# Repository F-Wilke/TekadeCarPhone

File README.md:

# TekadeCarPhone Hardware Design

This repository contains the KiCad source files for the **Tekade Car Phone** electronics, including the main baseboard, standalone UI board, libraries, production outputs, and reference documentation.

## Project Contents

- **Main design (CM4-based baseboard)**
  - Project: `ReleaseDeviceDigitalAudio.pro`
  - Top schematic: `ReleaseDeviceDigitalAudio.sch`
  - PCB: `ReleaseDeviceDigitalAudio.kicad_pcb`
  - Hierarchical sheets include:
    - `RaspberryPiCM4.sch`
    - `PowerSupplyCM4.sch`
    - `AudioMixing.sch`
    - `BluetoothModule.sch`
    - `ControllerUIBoard.sch`
    - `7SegmentDriver.sch`
    - `LevelShift.sch`
    - `RTC.sch`

- **Standalone UI board**
  - Project: `UIBoardStandalone.pro`
  - Schematic: `UIBoardStandalone.sch`
  - PCB: `UIBoardStandalone.kicad_pcb`

- **Alternative/legacy CM3 files**
  - `RaspberryPiCM3.sch`
  - `PowerSupplyCM3.sch`

- **Production and supporting assets**
  - Gerbers: `Gerber/`
  - BOM history: `BOM/`
  - Component datasheets/reference designs: `Datasheets/`
  - Custom symbols/footprints/libs: `libs/`

## Main Components and Their Roles

The CM4 baseboard design is split into functional blocks. The key components used in each block are:

- **Host compute module (`RaspberryPiCM4.sch`)**
  - Raspberry Pi Compute Module 4 is the main processing unit and system controller.

- **User/control interface (`ControllerUIBoard.sch`)**
  - **ATmega4809-A** handles local UI/control tasks and bridges signals between peripherals and the CM4.
  - External connectors and protection/passive networks support buttons, status signals, and board-to-board interfaces.

- **Audio codec and analog audio path (`AudioMixing.sch`)**
  - **MAX98089ETN+** provides the main audio codec/mixing interface (digital audio to analog paths and vice versa).
  - Supporting passives, filtering, and clocking components condition and stabilize audio signals.

- **Bluetooth audio module (`BluetoothModule.sch`)**
  - **BM64/BM83 family module** provides Bluetooth audio connectivity and related control/status interfaces.
  - **APX803L** supervisor supports reset/monitoring behavior for reliable module startup.

- **Display driving (`7SegmentDriver.sch`)**
  - **CD4514BM** and **CD4511BPWR** perform decoding/drive logic for 7-segment display control.
  - **ULN2003F12FN-7** transistor arrays provide higher-current sink drive for display segments/digits.

- **Real-time clock (`RTC.sch`)**
  - **PCF85063A** keeps time while system power is cycled.
  - Battery backup and crystal network maintain RTC operation.

- **Power entry and regulation (`PowerSupplyCM4.sch`)**
  - Automotive supply protection is implemented with TVS/clamp and filtering stages.
  - Switching/regulation and control circuitry generate stable board rails (for example +5V and +3.3V domains used by subsystems).

## Tooling

- Project files are in a legacy KiCad format (`.pro` and `EESchema Schematic File Version 4`).
- Open `.pro` projects in KiCad to browse schematics, PCB layout, and regenerate outputs.
- If using newer KiCad versions, open files carefully to avoid unintentionally migrating legacy project formats.

## Typical Workflow

1. Open `ReleaseDeviceDigitalAudio.pro` (or `UIBoardStandalone.pro`) in KiCad.
2. Review/update schematic sheets.
3. Update PCB from schematic and run DRC/ERC.
4. Regenerate fabrication outputs (Gerber + drill) and update BOM as needed.

## Notes

- This repository is focused on **hardware design artifacts**; firmware/software sources are not included.
- Some files with `-bak` suffix are backup snapshots.

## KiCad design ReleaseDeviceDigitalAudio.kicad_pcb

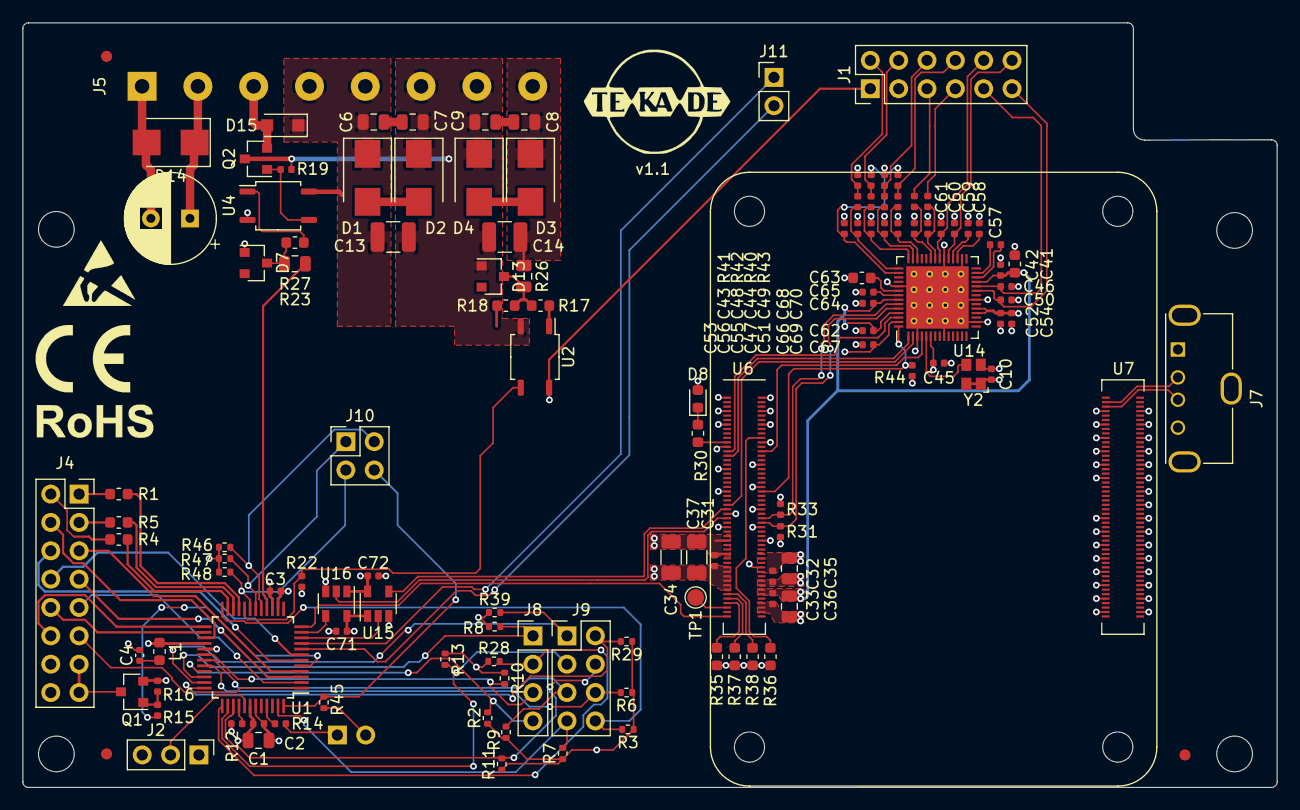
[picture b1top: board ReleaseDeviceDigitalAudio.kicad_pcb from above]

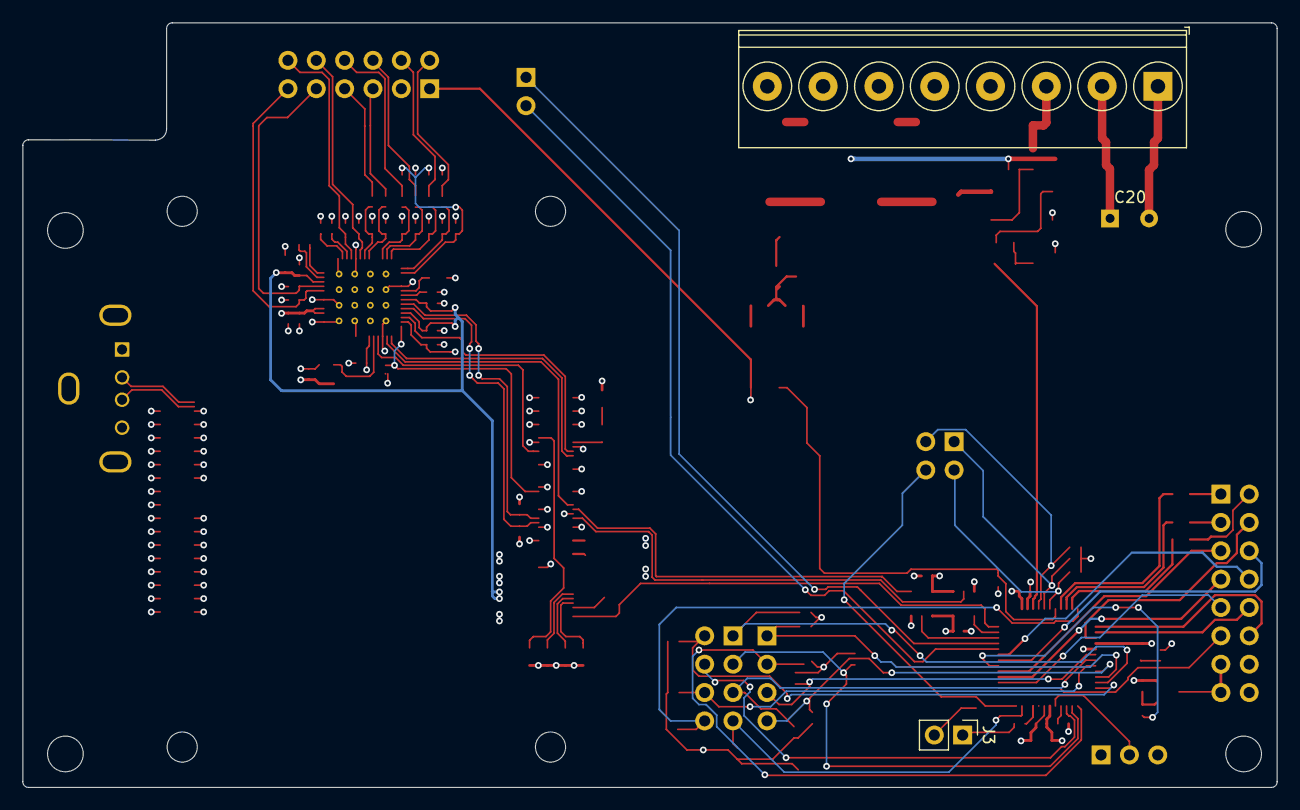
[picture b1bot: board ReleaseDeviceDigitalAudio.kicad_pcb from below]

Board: 4 copper layers, 112.4 x 68.5 mm, 129 parts (2 on the bottom side), 105 nets.

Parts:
C1: 4u7/16V/X7R; C_0805_2012Metric
C2, C3, C4, C10, C31, C32, C33, C42, C71, C72: 100n/16V/X7R; C_0402_1005Metric
C6, C7, C8, C9: 4n7/100V/X7R; C_0805_2012Metric
C13, C14: 10u/50V/X7R; C_1210_3225Metric
C20: 220u/25V; CP_Radial_D8.0mm_P3.50mm
C34, C37: 47u/10V/X5R; C_1206_3216Metric
C35, C36: 22u/10V/X5R; C_0805_2012Metric
C41: 10u/6V3/X5R; C_0603_1608Metric
C43, C44, C45, C48, C49, C52, C53, C54, C57, C58, C59, C62, C64, C65, C67, C68, C70: 1u/6V3/X5R; C_0402_1005Metric
C46, C47, C50, C51, C55, C56, C60, C61, C66, C69: 10p/50V/C0G; C_0402_1005Metric
C63: 2u2/6V3/X5R; C_0603_1608Metric
D1, D3: SMBJ28A-13-F; D_SMB
D2, D4, D14: SMBJ14A-13-F; D_SMB
D7: BZX84B5V1-7-F; SOT-23-2-DiodesInc
D8: LED_GRN; LED_0603_1608Metric
D13: BZX84B12-7-F; SOT-23-2-DiodesInc
D15: 1N4148WQ-7-F; D_SOD-123F
H1, H2, H3, H4: MountingHole; MountingHole_3.2mm_M3_DIN965
J1: Conn_02x06_Odd_Even; PinHeader_2x06_P2.54mm_Vertical
J2: ATMEGA_PROG; PinHeader_1x03_P2.54mm_Vertical
J3: SignalStrength; PinHeader_1x02_P2.54mm_Vertical
J4: UIBoardCON1; PinSocket_2x08_P2.54mm_Vertical
J5: Phoenix_PTS-1,5-8-5.0-H; TerminalBlock_Phoenix_PTS-1,5-8-5.0-H_1x08_P5.00mm_Horizont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
J7: USB_A; USB_A_Molex_105057_Vertical
J8: Conn_01x04; PinHeader_1x04_P2.54mm_Vertical
J9: Conn_02x04_Odd_Even; PinHeader_2x04_P2.54mm_Vertical
J10: Conn_02x02_Odd_Even; PinHeader_2x02_P2.54mm_Vertical
J11: Conn_01x02; PinHeader_1x02_P2.54mm_Vertical
L1: Ferrit/470R/1A/0,2R; L_0603_1608Metric
Q1: BSS314PEH6327XTSA1; SOT-23
Q2: SI2316BDS-T1-GE3; SOT-23
R1, R4, R5: 150R/1%; R_0603_1608Metric
R2, R3, R6, R7, R8, R9, R10, R11, R13, R28, R29, R39, R45, R46, R47, R48: 22k/1%; R_0402_1005Metric
R12: 100k/1%; R_0402_1005Metric
R14: 15k; R_0402_1005Metric
R15: 100R/1%; R_0402_1005Metric
R16, R19: 47k/1%; R_0402_1005Metric
R17, R18, R30: 1k/1%; R_0603_1608Metric
R22, R44: 10k/1%; R_0402_1005Metric
R23: 68R/1%; R_0805_2012Metric
R26: 150R/1%; R_0805_2012Metric
R27: 360R/1%; R_0603_1608Metric
R31, R33: NA; R_0402_1005Metric
R35, R36, R38: NA; R_0603_1608Metric
R37: 0R; R_0603_1608Metric
R40, R41, R42, R43: 2k2/1%; R_0402_1005Metric
TP1: CM4PWR; TestPoint_Pad_D1.5mm
U1: ATmega4809-A; TQFP-48_7x7mm_P0.5mm
U2, U4: VOMA617A; SOP-4_3.8x4.1mm_P2.54mm
U6: CM4_Connectors_Part1; CM4-Part1
U7: CM4_Connectors_Part2; CM4-Part2
U14: MAX98089ETN+; QFN-56_EP_7x7_Pitch0.4mm
U15, U16: SN74LV1T126; SOT-23-5
Y2: WE_830208220101; WE_IQXO-791

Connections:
+1V8: C33.1, C36.1, C41.1, C42.1, C62.1, C64.1, U6.88, U6.90, U14.25, U14.50, U14.53
+3V3: C10.1, C32.1, C35.1, C45.1, C52.1, C54.1, C67.1, C72.1, D8.2, R31.1, R33.1, R44.1, U6.78, U6.84, U6.86, U14.6, U14.18, U14.19, U14.55, U15.1, U16.5, Y2.1, Y2.4
+5V: C1.2, C2.1, C3.1, C20.1, C31.1, C34.1, C37.1, C71.1, D14.1, J1.1, J2.1, J4.14, J4.16, J5.2, J7.1, L1.1, Q1.2, R2.1, R3.1, R6.1, R7.1, R8.1, R9.1, R10.1, R11.1, R12.1, R13.1, R16.1, R28.1, R29.1, R39.1, U1.14, U1.28, U1.42, U2.4, U6.77, U6.79, U6.81, U6.83, U6.85, U6.87, U15.5, U16.1
+BATT: C6.1, C13.1, D1.1, D15.1, J5.4, J5.5, U4.4
-BATT: C7.2, C9.2, C13.2, C14.2, D2.1, D4.1, D13.2, J5.6, J5.7, Q2.3, R19.1, U2.2
/AudioMAX98089/I2S2_SD_CLK: U6.49, U14.2
/AudioMAX98089/I2S2_SD_IN: U6.25, U14.54
/AudioMAX98089/I2S2_SD_OUT: U6.27, U14.1
/AudioMAX98089/I2S2_SD_WS: U6.26, U14.4
/AudioMAX98089/MAX_MIC1N: C44.1, C47.1, U14.41
/AudioMAX98089/MAX_MIC1P: C49.1, C51.1, U14.40
/AudioMAX98089/MAX_MIC2N: C43.1, C56.1, U14.43
/AudioMAX98089/MAX_MIC2P: C48.1, C55.1, U14.42
/AudioMAX98089/MAX_MICBIAS: C53.1, R42.2, R43.1, U14.44
/AudioMAX98089/MCLK: U14.5, Y2.3
/Audio_Handset_Out_L: C60.1, J1.12, U14.33
/Audio_Handset_Out_R: C61.1, J1.10, U14.35
/Audio_Master_Out_L: C46.1, J1.9, U14.24
/Audio_Master_Out_R: C50.1, J1.11, U14.23
/ControllerUIBoard/5V_BL: J4.13, J4.15, Q1.3
/ControllerUIBoard/7Seg_Driver_BI: J4.4, U1.27
/ControllerUIBoard/7seg_dec_D1: J4.11, U1.1
/ControllerUIBoard/7seg_dec_D2: J4.7, U1.3
/ControllerUIBoard/7seg_dec_D3: J4.5, U1.4
/ControllerUIBoard/7seg_dec_D4: J4.9, U1.2
/ControllerUIBoard/7seg_dr_A: J4.6, U1.6
/ControllerUIBoard/7seg_dr_B: J4.12, U1.25
/ControllerUIBoard/7seg_dr_C: J4.10, U1.26
/ControllerUIBoard/7seg_dr_D: J4.8, U1.7
/ControllerUIBoard/AVRRESET: R12.2, U1.40
/ControllerUIBoard/Button_0: J9.7, R7.2, U1.47
/ControllerUIBoard/Button_1: J8.1, R8.2, U1.34
/ControllerUIBoard/Button_2: J9.1, R39.2, U1.35
/ControllerUIBoard/Button_3: J9.2, R29.2, U1.36
/ControllerUIBoard/Button_4: J8.2, R28.2, U1.37
/ControllerUIBoard/Button_5: J9.3, R13.2, U1.38
/ControllerUIBoard/Button_6: J9.4, R11.2, U1.39
/ControllerUIBoard/Button_7: J8.3, R10.2, U1.30
/ControllerUIBoard/Button_8: J9.5, R9.2, U1.31
/ControllerUIBoard/Button_9: J9.6, R6.2, U1.32
/ControllerUIBoard/Button_G: J10.1, R47.1, U1.18
/ControllerUIBoard/Button_M: J9.8, R3.2, U1.24
/ControllerUIBoard/Button_P: J10.3, R48.1, U1.19
/ControllerUIBoard/Button_R: J8.4, R2.2, U1.33
/ControllerUIBoard/Button_S: J10.2, R46.1, U1.17
/ControllerUIBoard/Button_X: J10.4, R45.1, U1.48
/ControllerUIBoard/Hoerer_1: J11.2, U1.8
/ControllerUIBoard/Hoerer_2: J11.1, U1.9
/ControllerUIBoard/IGNITION_SENSE: R22.2, U1.20, U2.3
/ControllerUIBoard/LED_GN: J4.2, R4.2
/ControllerUIBoard/LED_RD: J4.3, R5.2
/ControllerUIBoard/LED_YL: J4.1, R1.2
/ControllerUIBoard/RPI_RUN: U1.12, U6.99
/ControllerUIBoard/Signal_Strength_Dial_+: J3.1, R14.1
/ControllerUIBoard/UART1_RX: U1.11, U15.4
/ControllerUIBoard/UART1_TX: U1.10, U16.2
/ControllerUIBoard/UPDI_DATA: J2.2, U1.41
/HeadsetMicInN: C44.2, J1.6, R40.1
/HeadsetMicInP: C49.2, J1.8, R43.2
/Line_In_L: C70.2, J1.7
/Line_In_R: C68.2, J1.5
/MasterMicInN: C43.2, J1.2, R41.1
/MasterMicInP: C48.2, J1.4, R42.1
/PowerSupply/Bell_In: R23.1, U1.16
/PowerSupply/IGNITION: C8.1, C14.1, D3.1, J5.8, R26.1
/PowerSupply/K1_GND: D15.2, J5.3, Q2.2
/RPiCM4/BT_nDisable: R37.2, U6.91
/RPiCM4/EEPROM_nWP: R36.2, U6.20
/RPiCM4/GPIO10: R44.2, U6.44, U14.56
/RPiCM4/I2C1_SCL: R33.2, U6.56, U14.51
/RPiCM4/I2C1_SDA: R31.2, U6.58, U14.52
/RPiCM4/UART0_RX: U6.51, U16.4
/RPiCM4/UART0_TX: U6.55, U15.2
/RPiCM4/WL_nDisable: R38.2, U6.89
/RPiCM4/nRPIBOOT: R35.2, U6.93
GND: C1.1, C2.2, C3.2, C4.2, C10.2, C20.2, C31.2, C32.2, C33.2, C34.2, C35.2, C36.2, C37.2, C41.2, C42.2, C45.2, C46.2, C47.2, C50.2, C51.2, C52.2, C53.2, C54.2, C55.2, C56.2, C58.2, C59.2, C60.2, C61.2, C62.2, C63.2, C64.2, C65.2, C66.2, C67.2, C69.2, C71.2, C72.2, D7.2, D14.2, J1.3, J2.3, J3.2, J5.1, J7.4, J7.5, R22.1, R35.1, R36.1, R37.1, R38.1, R40.2, R41.2, R45.2, R46.2, R47.2, R48.2, U1.15, U1.29, U1.43, U4.2, U6.1, U6.2, U6.7, U6.8, U6.13, U6.14, U6.22, U6.23, U6.32, U6.33, U6.42, U6.43, U6.52, U6.53, U6.59, U6.60, U6.65, U6.66, U6.71, U6.74, U6.94, U6.96, U6.98, U7.107, U7.108, U7.113, U7.114, U7.119, U7.120, U7.125, U7.126, U7.131, U7.132, U7.137, U7.138, U7.144, U7.150, U7.155, U7.156, U7.161, U7.162, U7.167, U7.168, U7.173, U7.174, U7.179, U7.180, U7.185, U7.186, U7.191, U7.192, U7.197, U7.198, U14.3, U14.9, U14.16, U14.21, U14.30, U14.34, U14.47, U14.57, U15.3, U16.3, Y2.2
unnamed: C4.1, L1.2
unnamed: C6.2, C7.1
unnamed: C8.2, C9.1
unnamed: C57.1, U14.27
unnamed: C57.2, U14.26
unnamed: C58.1, U14.31
unnamed: C59.1, U14.32
unnamed: C63.1, U14.48
unnamed: C65.1, U14.49
unnamed: C66.1, C68.1, U14.37
unnamed: C69.1, C70.1, U14.36
unnamed: D1.2, D2.2
unnamed: D3.2, D4.2
unnamed: D7.1, R23.2, R27.1
unnamed: D8.1, R30.1
unnamed: D13.1, R17.2, R18.2, R26.2
unnamed: J7.2, U7.103
unnamed: J7.3, U7.105
unnamed: Q1.1, R15.1, R16.2
unnamed: Q2.1, R19.2, U4.3
unnamed: R1.1, U1.21
unnamed: R4.1, U1.23
unnamed: R5.1, U1.22
unnamed: R14.2, U1.45
unnamed: R15.2, U1.5
unnamed: R17.1, U2.1
unnamed: R27.2, U4.1
unnamed: R30.2, U6.21
unnamed: TP1.1, U6.95

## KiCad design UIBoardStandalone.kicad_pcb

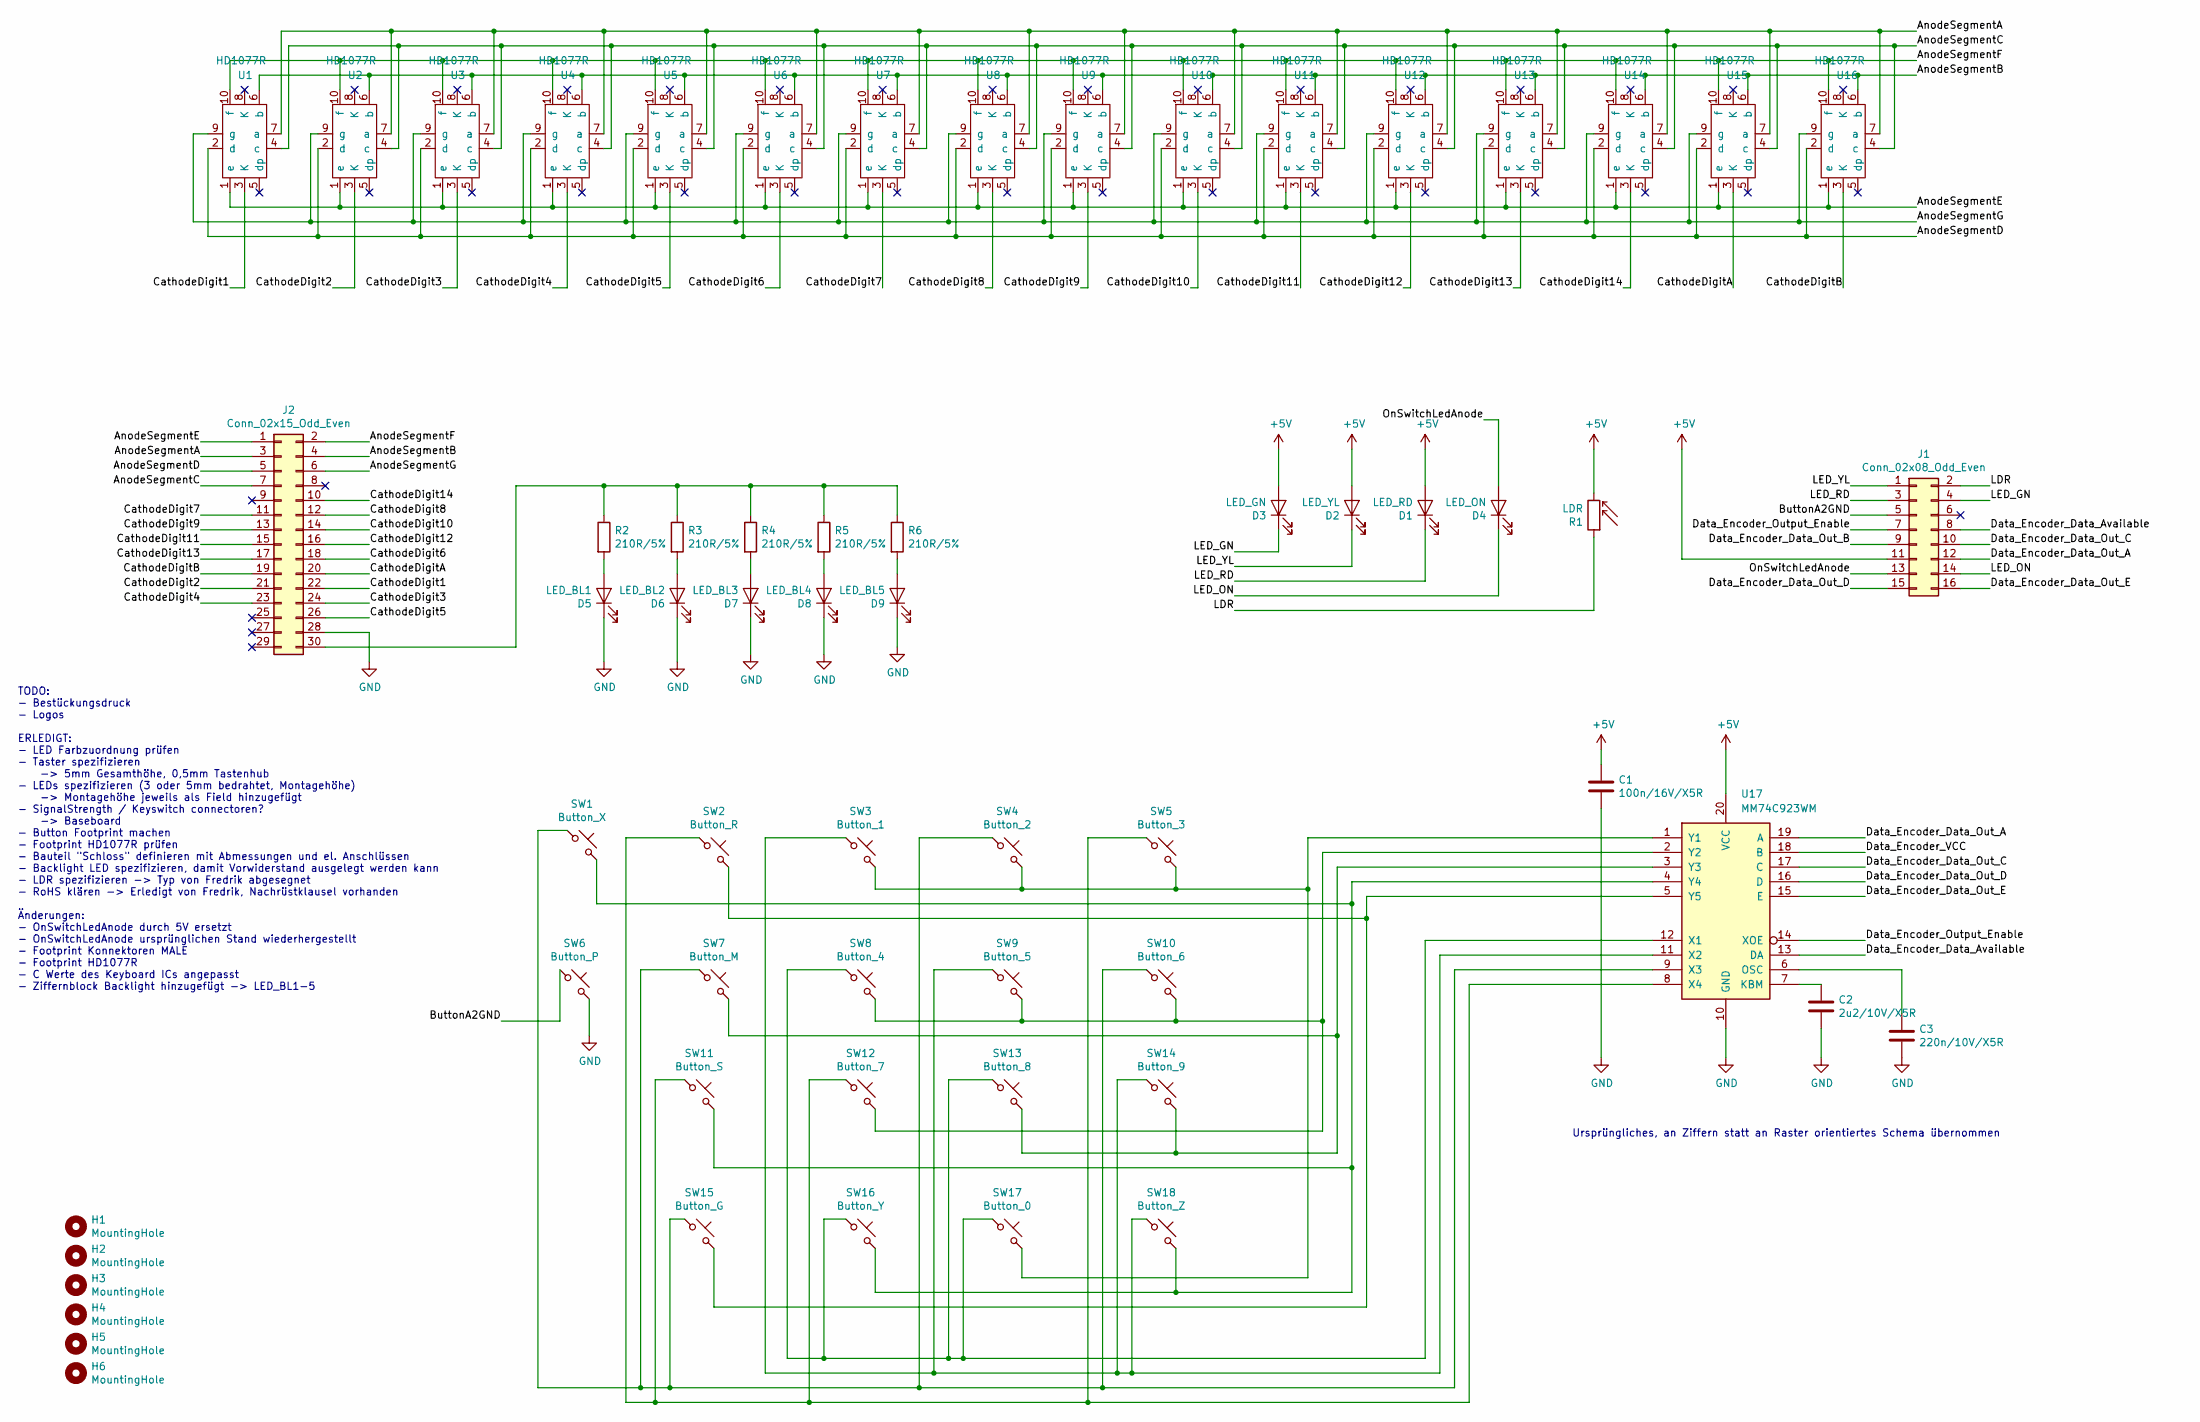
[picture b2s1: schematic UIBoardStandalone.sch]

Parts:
C1: 100n/16V/X5R; C_0603_1608Metric
C2: 2u2/10V/X5R; C_0603_1608Metric
C3: 220n/10V/X5R; C_0603_1608Metric
D1: LED_RD; LED_D5.0mm
D2: LED_YL; LED_D5.0mm
D3: LED_GN; LED_D5.0mm
D4: LED_ON; LED_D3.0mm
D5: LED_BL1; LED_D3.0mm
D6: LED_BL2; LED_D3.0mm
D7: LED_BL3; LED_D3.0mm
D8: LED_BL4; LED_D3.0mm
D9: LED_BL5; LED_D3.0mm
H1, H2, H3, H4, H5, H6: MountingHole; MountingHole_3.2mm_M3_DIN965
J1: Conn_02x08_Odd_Even; PinHeader_2x08_P2.54mm_Vertical
J2: Conn_02x15_Odd_Even; PinHeader_2x15_P2.54mm_Vertical
R1: LDR; R_LDR_4.9x4.2mm_P2.54mm_Vertical
R2, R3, R4, R5, R6: 210R/5%; R_0603_1608Metric
SW1: Button_X; SW_Push_CK_KST2x1G
SW2: Button_R; SW_Push_CK_KST2x1G
SW3: Button_1; SW_Push_CK_KST2x1G
SW4: Button_2; SW_Push_CK_KST2x1G
SW5: Button_3; SW_Push_CK_KST2x1G
SW6: Button_P; SW_Push_CK_KST2x1G
SW7: Button_M; SW_Push_CK_KST2x1G
SW8: Button_4; SW_Push_CK_KST2x1G
SW9: Button_5; SW_Push_CK_KST2x1G
SW10: Button_6; SW_Push_CK_KST2x1G
SW11: Button_S; SW_Push_CK_KST2x1G
SW12: Button_7; SW_Push_CK_KST2x1G
SW13: Button_8; SW_Push_CK_KST2x1G
SW14: Button_9; SW_Push_CK_KST2x1G
SW15: Button_G; SW_Push_CK_KST2x1G
SW16: Button_Y; SW_Push_CK_KST2x1G
SW17: Button_0; SW_Push_CK_KST2x1G
SW18: Button_Z; SW_Push_CK_KST2x1G
U1, U2, U3, U4, U5, U6, U7, U8, U9, U10, U11, U12, U13, U14, U15, U16: HD1077R; 7SegmentLED_HD1077R
U17: MM74C923WM; SOIC-20W_7.5x12.8mm_P1.27mm

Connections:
+5V: C1.1, D1.2 (A), D2.2 (A), D3.2 (A), J1.11, R1.2, U17.20 (VCC)
/AnodeSegmentA: J2.3, U1.7 (a), U2.7 (a), U3.7 (a), U4.7 (a), U5.7 (a), U6.7 (a), U7.7 (a), U8.7 (a), U9.7 (a), U10.7 (a), U11.7 (a), U12.7 (a), U13.7 (a), U14.7 (a), U15.7 (a), U16.7 (a)
/AnodeSegmentB: J2.4, U1.6 (b), U2.6 (b), U3.6 (b), U4.6 (b), U5.6 (b), U6.6 (b), U7.6 (b), U8.6 (b), U9.6 (b), U10.6 (b), U11.6 (b), U12.6 (b), U13.6 (b), U14.6 (b), U15.6 (b), U16.6 (b)
/AnodeSegmentC: J2.7, U1.4 (c), U2.4 (c), U3.4 (c), U4.4 (c), U5.4 (c), U6.4 (c), U7.4 (c), U8.4 (c), U9.4 (c), U10.4 (c), U11.4 (c), U12.4 (c), U13.4 (c), U14.4 (c), U15.4 (c), U16.4 (c)
/AnodeSegmentD: J2.5, U1.2 (d), U2.2 (d), U3.2 (d), U4.2 (d), U5.2 (d), U6.2 (d), U7.2 (d), U8.2 (d), U9.2 (d), U10.2 (d), U11.2 (d), U12.2 (d), U13.2 (d), U14.2 (d), U15.2 (d), U16.2 (d)
/AnodeSegmentE: J2.1, U1.1 (e), U2.1 (e), U3.1 (e), U4.1 (e), U5.1 (e), U6.1 (e), U7.1 (e), U8.1 (e), U9.1 (e), U10.1 (e), U11.1 (e), U12.1 (e), U13.1 (e), U14.1 (e), U15.1 (e), U16.1 (e)
/AnodeSegmentF: J2.2, U1.10 (f), U2.10 (f), U3.10 (f), U4.10 (f), U5.10 (f), U6.10 (f), U7.10 (f), U8.10 (f), U9.10 (f), U10.10 (f), U11.10 (f), U12.10 (f), U13.10 (f), U14.10 (f), U15.10 (f), U16.10 (f)
/AnodeSegmentG: J2.6, U1.9 (g), U2.9 (g), U3.9 (g), U4.9 (g), U5.9 (g), U6.9 (g), U7.9 (g), U8.9 (g), U9.9 (g), U10.9 (g), U11.9 (g), U12.9 (g), U13.9 (g), U14.9 (g), U15.9 (g), U16.9 (g)
/ButtonA2GND: J1.5, SW6.1
/CathodeDigit1: J2.22, U1.3 (K)
/CathodeDigit2: J2.21, U2.3 (K)
/CathodeDigit3: J2.24, U3.3 (K)
/CathodeDigit4: J2.23, U4.3 (K)
/CathodeDigit5: J2.26, U5.3 (K)
/CathodeDigit6: J2.18, U6.3 (K)
/CathodeDigit7: J2.11, U7.3 (K)
/CathodeDigit8: J2.12, U8.3 (K)
/CathodeDigit9: J2.13, U9.3 (K)
/CathodeDigit10: J2.14, U10.3 (K)
/CathodeDigit11: J2.15, U11.3 (K)
/CathodeDigit12: J2.16, U12.3 (K)
/CathodeDigit13: J2.17, U13.3 (K)
/CathodeDigit14: J2.10, U14.3 (K)
/CathodeDigitA: J2.20, U15.3 (K)
/CathodeDigitB: J2.19, U16.3 (K)
/Data_Encoder_Data_Available: J1.8, U17.13 (DA)
/Data_Encoder_Data_Out_A: J1.12, U17.19 (A)
/Data_Encoder_Data_Out_B: J1.9
/Data_Encoder_Data_Out_C: J1.10, U17.17 (C)
/Data_Encoder_Data_Out_D: J1.15, U17.16 (D)
/Data_Encoder_Data_Out_E: J1.16, U17.15 (E)
/Data_Encoder_Output_Enable: J1.7, U17.14 (XOE)
/Data_Encoder_VCC: U17.18 (B)
/LDR: J1.2, R1.1
/LED_GN: D3.1 (K), J1.4
/LED_ON: D4.1 (K), J1.14
/LED_RD: D1.1 (K), J1.3
/LED_YL: D2.1 (K), J1.1
/OnSwitchLedAnode: D4.2 (A), J1.13
GND: C1.2, C2.2, C3.2, D5.1 (K), D6.1 (K), D7.1 (K), D8.1 (K), D9.1 (K), J2.28, SW6.2, U17.10 (GND)
unnamed: C2.1, U17.7 (KBM)
unnamed: C3.1, U17.6 (OSC)
unnamed: D5.2 (A), R2.2
unnamed: D6.2 (A), R3.2
unnamed: D7.2 (A), R4.2
unnamed: D8.2 (A), R5.2
unnamed: D9.2 (A), R6.2
unnamed: J2.30, R2.1, R3.1, R4.1, R5.1, R6.1
unnamed: SW1.1, SW4.1, SW7.1, SW10.1, SW15.1, U17.9 (X3)
unnamed: SW1.2, SW11.2, SW16.2, SW18.2, U17.4 (Y4)
unnamed: SW8.2, SW9.2, SW10.2, SW12.2, U17.2 (Y2)
unnamed: SW2.1, SW5.1, SW11.1, SW12.1, U17.8 (X4)
unnamed: SW8.1, SW13.1, SW16.1, SW17.1, U17.12 (X1)
unnamed: SW7.2, SW13.2, SW14.2, U17.3 (Y3)
unnamed: SW3.1, SW9.1, SW14.1, SW18.1, U17.11 (X2)
unnamed: SW2.2, SW15.2, U17.5 (Y5)
unnamed: SW3.2, SW4.2, SW5.2, SW17.2, U17.1 (Y1)

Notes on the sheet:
Ursprüngliches, an Ziffern statt an Raster orientiertes Schema übernommen
TODO: - Bestückungsdruck - Logos ERLEDIGT: - LED Farbzuordnung prüfen - Taster spezifizieren -> 5mm Gesamthöhe, 0,5mm Tastenhub - LEDs spezifizieren (3 oder 5mm bedrahtet, Montagehöhe) -> Montagehöhe jeweils als Field hinzugefügt - SignalStrength / Keyswitch connectoren? -> Baseboard - Button Footp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

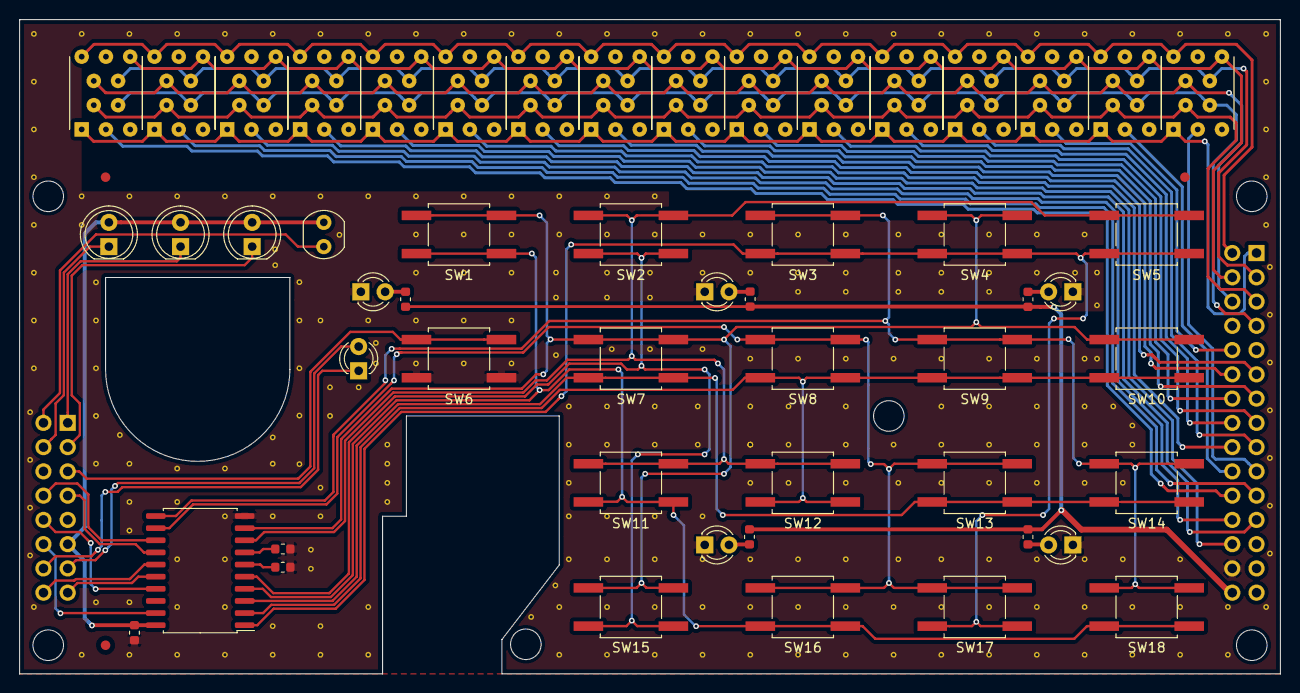
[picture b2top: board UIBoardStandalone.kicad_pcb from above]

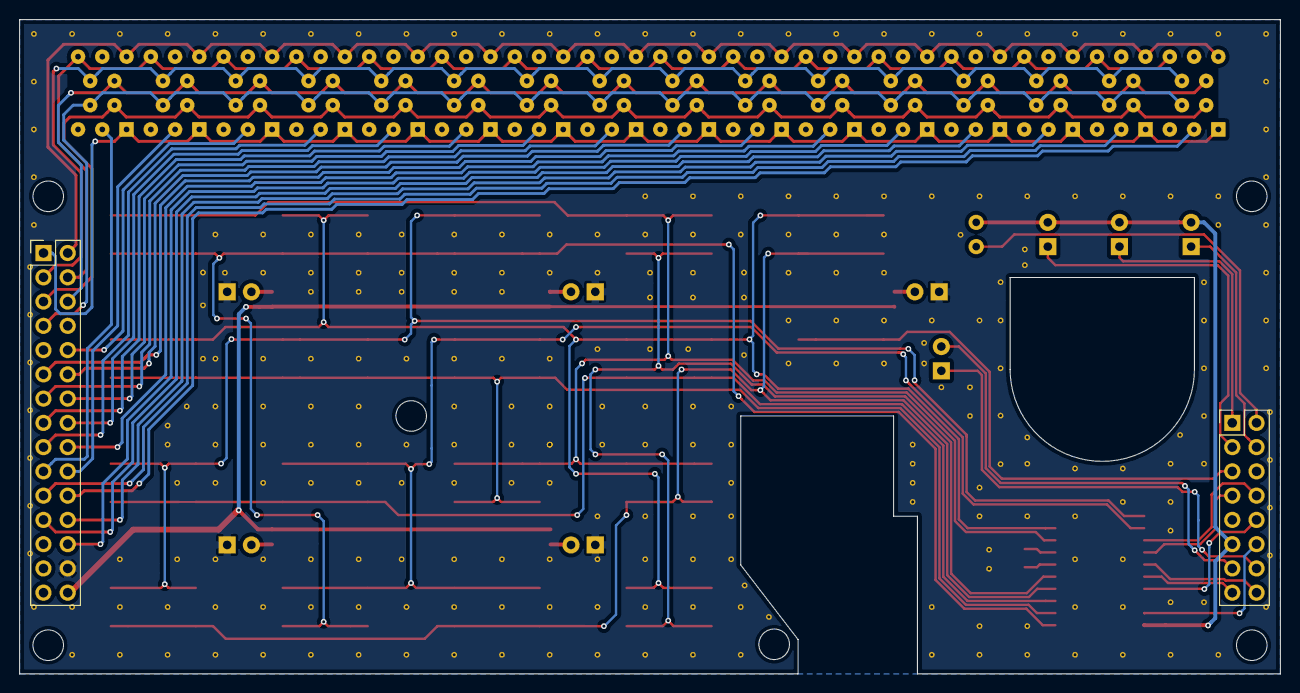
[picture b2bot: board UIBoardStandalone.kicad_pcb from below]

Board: 2 copper layers, 132.0 x 68.5 mm, 61 parts (2 on the bottom side), 55 nets.

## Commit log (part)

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2021-06-10 Name changes: RN52 -> BM83 removal of legacy USB Labels
2021-06-13 [modified:] Datasheet cleanup [modified:] lib cleanup [fix:] removed voltmeter from uiboard [fix:] mic audio jack terminal mix-up
2021-06-15 -Symbole angepasst -Audio Mixing umgezeichnet -Audio Mixing teilweise geprüft
2021-06-16 Alle Libs zusammengefasst in TeKaDe.lib Power Supply mit Standartbauteilen (nicht das Import Zeugs)
2021-06-16 - Alles aus rescue Lib noch in neue Lib gepackt
2021-06-17 Footprint Libs wieder hinzugefügt Bugfix: 5VD Netz in 5V geändert
2021-06-22 Footprints überarbeitet MAX98089 mit 3V3 Speaker Versorgung machen, damit hier nicht 5V geroutet werden müssen
2021-06-22 hierarchical layout: RPi, Bluetooth module bus implementation Switch to RPi MiniUart
2021-06-24 PowerSupply update
2021-06-24 Mehr Hierarchie
2021-06-25 [modified:] RTC revision [add:] RPis second I2C port
2021-06-25 [add:] MAX98089 Line Out caps
2021-06-25 [modified:] RPI I2C splitting
2021-06-25 Kleinigkeiten
2021-06-25 BN83 Zwischenstand
2021-06-26 [added:] 5V buck converter enable circuit [added:] RPi power up circuit
2021-06-27 [add:] second RPi uart [add:] ATMEGA RPi UART communication incl. level shifting
2021-06-27 [modified:] Display driving cleanup
2021-06-27 [fix:] differential microphone input
2021-06-27 [fix:] corrected CD4515 to CD4514
2021-06-28 - Busbenennungen angepasst - Kommentare angefügt
2021-06-28 [modified:] merge precautions
2021-06-29 [fix:] merge cleanup
2021-06-29 [modified:] Digit nomenclature clarification
2021-07-07 - MAX98089 fertig - Footprints von MAX und Oszilator angepasst - Pullups für I2C hinzugefügt - Bus / Signal Namen Fehlzuweisungen ausgebessert
2021-07-07 - Earth durch GND an den letzten Stellen ersetzt
2021-07-09 - BT fertig, warten auf Rueckmeldung von Microchip - CM3 fast fertig - diverse Kleinigkeiten
2021-07-10 - CM3 durch CM4 ersetzt - Spannungsregler für 3,3 und 1,8V entfernt, da nun von CM4 erzeugt - RTC IC getauscht
2021-07-10 - Files aufgeraeumt
2021-07-10 - 0R Bruecken hinzugefuegt - viele Detailinfos
2021-07-11 - Bus Topologie entfernt - Levelshifter auf eigenes Blatt, abgeschlossen
2021-07-11 [added:] ATMEGA 4809 integration
2021-07-11 - Zwischenstand Display Driving
2021-07-11 Umsortiert
2021-07-11 [modified:] uln2003 package swap [modified:] Display nomenclature update
2021-07-11 - Display Driving abgeschlossen
2021-07-12 - CM4 update - Todo Liste auf Hauptschaltplan hinzugefügt
2021-07-13 - Selbsthalteschaltung vorerst fertig, Simulation folgt
2021-07-14 - Kleinigkeiten
2021-07-14 - ESD Schutz Zündung
2021-07-15 - ATmega überarbeitet - Alle offenen Punkte zusammengefasst
2021-07-15 - Platzoptimierungen
2021-08-03 Notes extended removed level shift for RPi.PWR_EN
2021-08-04 [fix:] general troublespots -> notes
2021-08-07 - Kommentare aktualisiert
2021-08-13 - Footprint HD1077R
2021-08-16 - Outline und erste Plazierungen
2021-08-16 - Steckverbinder auf Rueckseite gespiegelt
2021-08-19 - Outline / Postionierung Zwischenstand
2021-08-19 - erster Stand für Abmessungen
2021-08-23 [fix:] measurement errors [add:] backlight LEDs
2021-09-17 [mod:] updated keyboard controller caps, notes
2021-09-18 [mod:] BM83 issues resolved: MCLK, unused pins
2021-09-19 [mod:] Atmega issues resolved: Programming interface, self cutoff
2021-09-20 [mod:] BM83.MFB connection removed
2021-09-20 [mod:] UIBoard buttons specified
2021-09-22 - Anpassungen ToDos und kleinere Änderungen
2021-09-25 [mod:] Note updates, KeySwitch mechanical definition
2021-09-25 [mod:] note updates
2021-10-12 - Erster Stand UI Board Layout
2021-10-12 - .DS_Store aus repo entfernt
2021-10-12 - Libs hinzugefügt / merge fertig
2021-10-17 [add:] LED specifications
2021-10-17 [mod:] MCLK input to MAX98089 from BM83 at 12.28MHz
2021-10-18 [add:] explanations omitted in last commit
2021-10-27 [fix:] LED definition bug
2021-10-27 - R Values hinzugefügt - Text aktualisiert - vorläufe BOM hinzugefügt
2021-10-29 - UI Backlight schaltbar gemacht, erster Entwurf, +5VA Symbol durch Label ersetzt
2021-10-31 [mod:] socket pin mirroring
2021-11-01 - Signalnamen korrigiert, Spiegelung geprüft
2021-11-01 - Schaltbare BL Versorgung fertig - kleinere Value Anpassungen - Finale Annotation
2021-11-02 - Bauteile konsolidiert
2021-11-02 - BOM updates
2021-11-02 - fix: footprint getauscht
2021-11-02 - SW1 entfernt
2021-11-02 - Wert und Footprint der LED Vorwiderstaende angepasst
2021-11-02 - Steckverbinder Signal und Lock aktualisiert
2021-11-04 - Datenblaetter aktualisiert
2021-11-04 - BOMs aktualisiert
2021-11-04 - minimale Datenblatt und BOM Korrekturen
2021-11-04 - .DS_Store wieder entfernt
2021-11-04 - vorlaeufige Bauteil Positionierung
2021-11-04 - noch ein altes Datenblatt...
2021-11-10 BOM update
2021-11-11 - Board auf 4 Lagen umgestellt, GND und 5V Lagen eingefügt
2021-11-11 - neue Stecker hinzugefügt, Annotation überall entsprechend angepasst Footprint fehlt noch
2021-11-11 - Footprints inkl. 3D model aller Steckverbinder fertig
2021-11-11 - Ausschnitt für BT Antenne und weitere Optimierungen
2021-11-28 - auf 20pol Audiostecker umgebaut
2021-12-01 - Layout Zwischenstand, UI Board Ansteuerung fast fertig - GPIOs von ATmega komplett umsortiert - Darlington Anschlüsse umsortiert
2021-12-28 - BT1 fixed
2022-01-07 - Layout MAX98 - Audiostecker Belegung angepasst
2022-01-08 - IRQ Pullup Spannung auf 3,3V
2022-01-12 - Letzter Zwischenstand vor Branch. Alles außer Spannungsversorgung und Zündung ist vorerst fertig.
2022-01-14 - Zwischenstand
2022-01-15 - Fix: Pinbelegung
2022-01-16 -Fix: Pad Offsets entfernt
2022-01-16 - Galvanische Trennung zu KFZ abgeschlossen
2022-01-16 - Merged Fix for ACM1211 footprint
2022-01-16 - Fiducials und Logos hinzugefügt
2022-01-17 - Fix: alle DRC Fehler bereinigt
2022-01-17 - Fix: Merged DRC fixes from 5VEXT branch
2022-01-17 - Eigene Masse Insel für Audio - Footprint Terminal PT durch PTS ersetzt (baut nur etwas tiefer)
2022-01-17 - Fix: Darlington Pad NICHT elektrisch verbinden!
2022-01-17 - merged Fix pad not on gnd
2022-01-17 - Pasten und Masken von Darlingtons und MAX angepasst
2022-01-17 - merged fix: max and darlington pads and paste
2022-01-18 - BOM und Feinheiten
2022-01-18 - Fix: no thermals auf GND Layer unter MAX
2022-01-19 - großes BOM update mit allen Bauteilen und Verfügbarkeiten geupdated
2022-01-19 - update
2022-01-20 - 1,5mm Connector aus BOM gestrichen, damit ist kein Platz für Bauteile unter CM4 - RTC neben das CM4 verschoben, da mit 1,75mm um 0,25mm zu hoch für unterhalb - BT1 von THT auf SMD Typ gewechselt (B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
2022-01-20 - merged Lib updates
2022-01-20 - BOM update fehlte in letztem commit
2022-01-20 Added logo + version number
2022-01-20 added logo, version
2022-01-21 - Gerber Export
2022-01-31 - Testpoints für BM83 USB hinzugefuegt
2022-02-18 - Reset IC fuer BM83 hinzugefuegt
2022-03-18 - BM64 Lib added
2022-03-22 - Schaltplan und BOM an BM64 angepasst
2022-03-30 Umbau auf BM64 zur Freigabe
2022-05-31 - CM4 Lib aufgeteilt - Gerber und BOM angepasst - Fix: SMD Bauteile waren teils als THT deklariert
2023-07-03 [add:] annotations, corrections from testing
2023-07-03 merge
2023-11-09 all the changes before BSA21 project
2023-11-09 first steps bsa31
2023-11-10 schematic changes up to layout import
2023-11-10 checkpoint: new schema, old layout
2023-11-10 layout first try
